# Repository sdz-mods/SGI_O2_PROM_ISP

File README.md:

# SGI O2 PROM ISP

In-system programmer for the SGI O2 system PROM. It which allows writing/dumping the system PROM via USB. This can be done at any point, with the system on or off.
Mechanically compatible with all O2 CPU modules.

## Installation instructions:

-remove Dallas socket

-remove flash IC

-solder the two FFCs

-solder Dallas socket back

-install Dallas IC

-solder the flash IC to the ISP

-mount ISP on top of Dallas IC, connect the two FFCs.

### Flashing/dumping PROM

```csh
python3 O2_FLASH_PROM.py --port COM38 --flash IP32_418_dump.bin --verify

Opening port: COM38

File : IP32_418_dump.bin  (524,288 bytes)

Flash: 524,288 bytes  |  Chunks: 128 × 4096 bytes

Flashing...

Flashing: [########################################] 100%

Flash complete.

Verifying...

Verifying: [########################################] 100%

Verify passed — flash contents match file.

python3 O2_FLASH_PROM.py --port /dev/ttyUSB0 --dump testdump.bin

Opening port: /dev/ttyUSB0

Dumping 524,288 bytes to: testdump.bin

Dumping: [########################################] 100%

Dump complete. Saved 524,288 bytes to 'testdump.bin'
```

## Contents

1.SCH_BRD - contains editable schematic and board files. Format is Eagle CAD, but they can be imported in other tools, like Kicad.

2.SCH_PDF- schematics in pdf format.

3.P&P - pick and place files

4.BOM

5.GERBER - gerber files

6.FIRMWARE - pre-built firmware to be flashed on the RP2040

7.FIRMWARE_SRC - firmware source code plus support files.

8.HOST_TOOL - host flashing script

9.PHOTOS - installation photos

## Notes

-There is a very high probabilty if you install this and flash a firmware, you won't be able to setenv -p or resetenv from PROM. This isn't related to the ISP, it happens even when swapping the flash ICs between two working motherboards.

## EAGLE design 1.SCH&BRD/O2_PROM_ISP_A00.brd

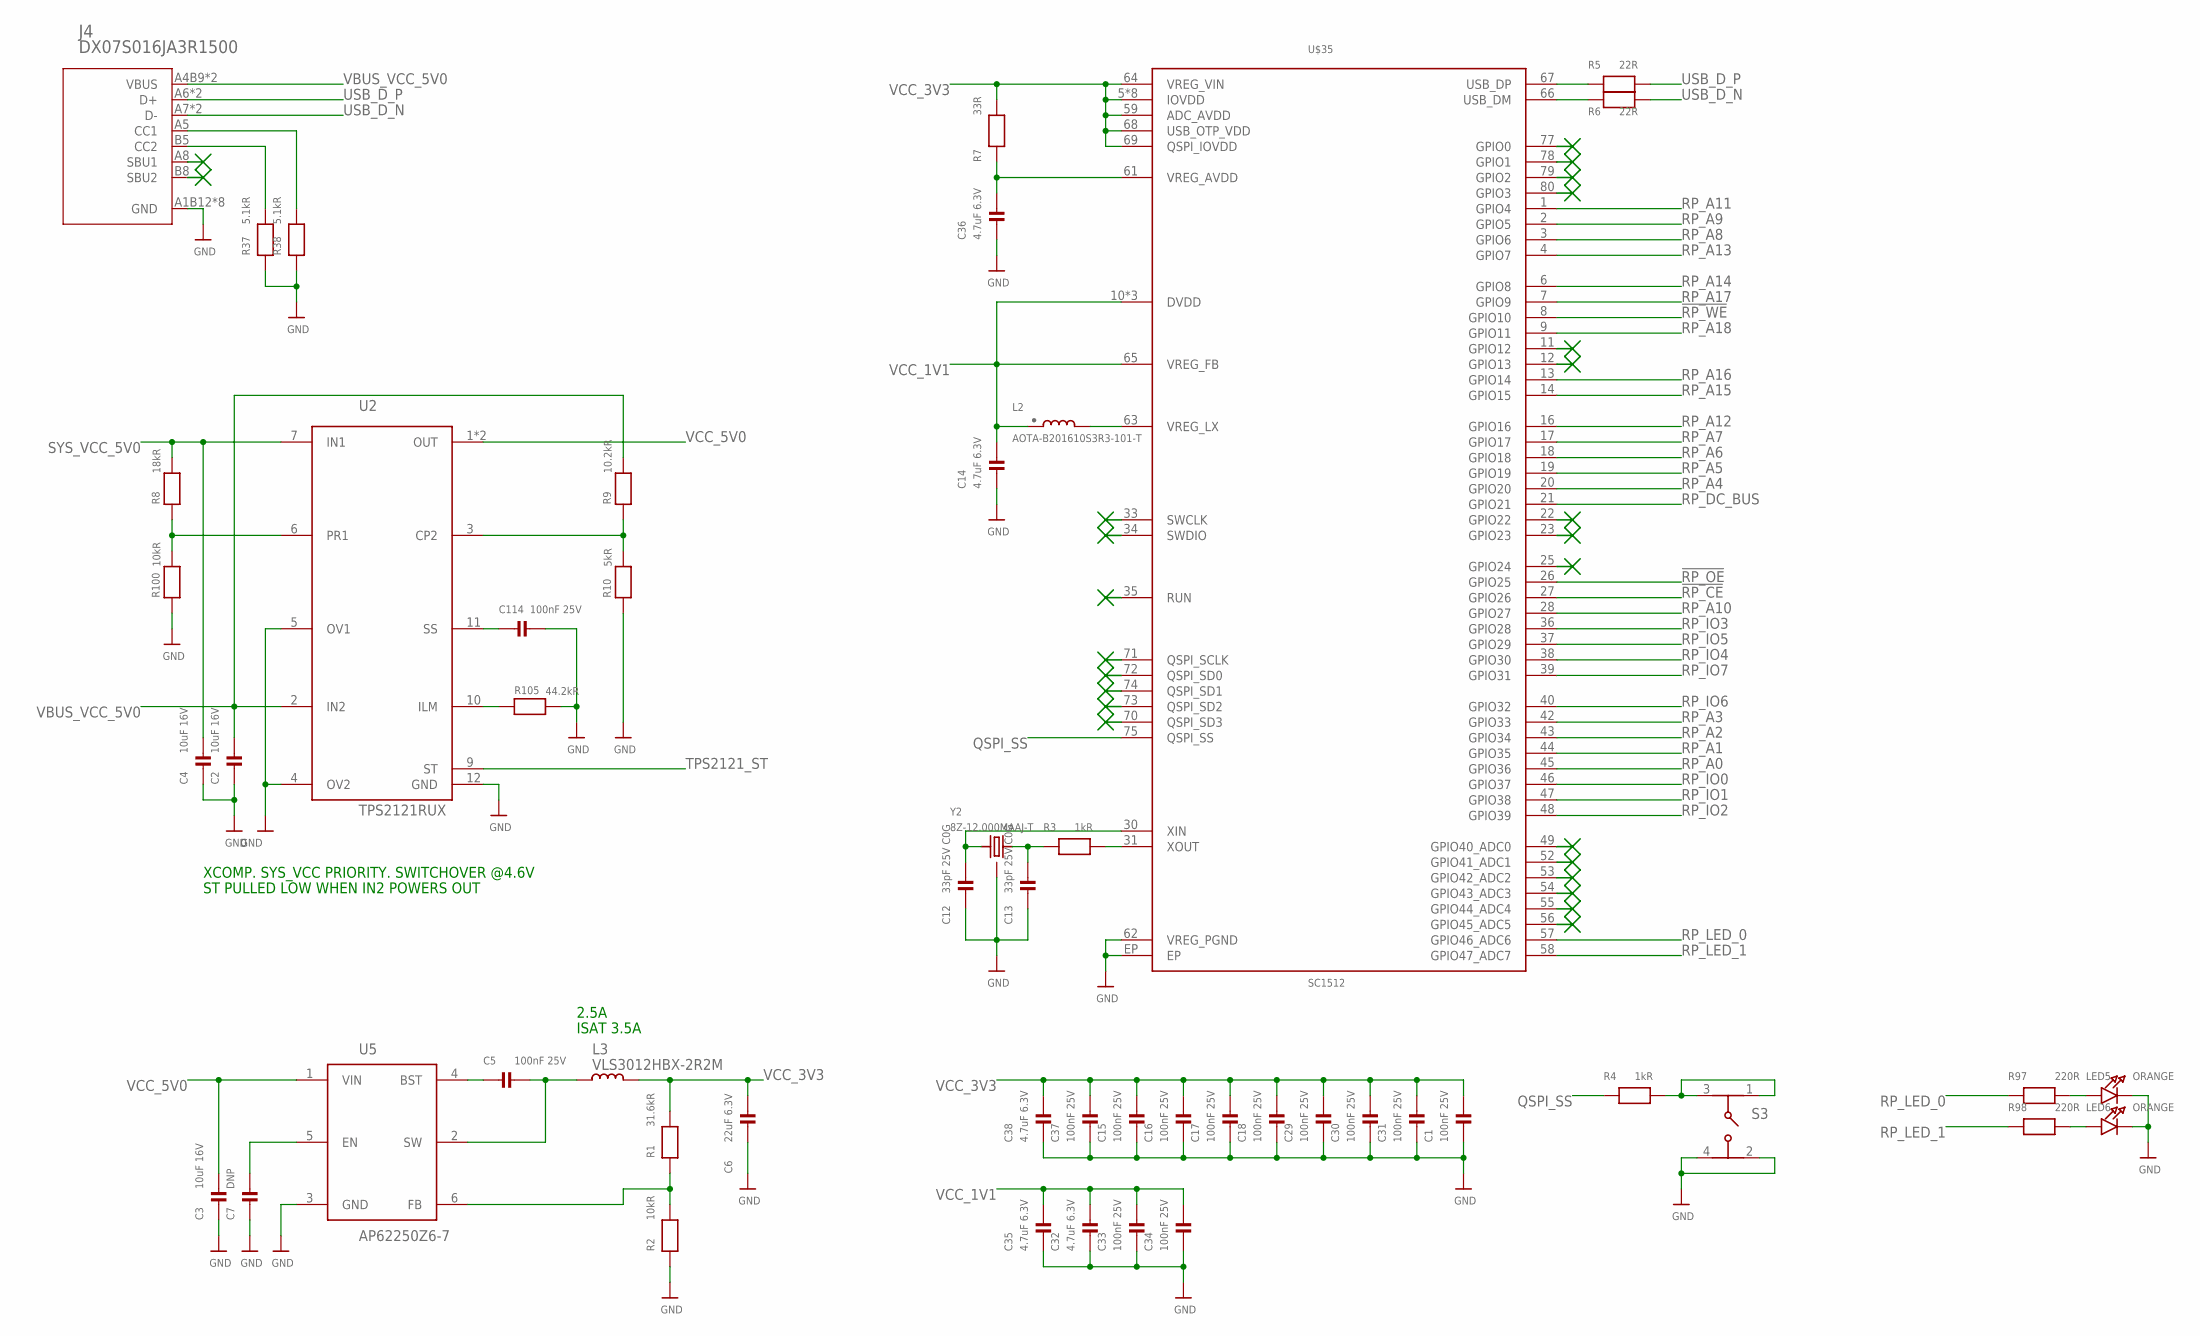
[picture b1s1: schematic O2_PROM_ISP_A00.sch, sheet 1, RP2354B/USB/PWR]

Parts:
C1, C5, C15, C16, C17, C18, C29, C30, C31, C33, C34, C37, C114: 100nF 25V; 0402D
C2, C3, C4: 10uF 16V; 0603D
C6: 22uF 6.3V; 0603D
C7: DNP; 0402D
C12, C13: 33pF 25V C0G; 0402D
C14, C32, C35, C36, C38: 4.7uF 6.3V; 0402D
J4: DX07S016JA3R1500
L2: AOTA-B201610S3R3-101-T; 0806
L3: VLS3012HBX-2R2M; VLS3012
LED5, LED6: ORANGE; CHIPLED_0402C
R1: 31.6kR; 0402D
R2, R100: 10kR; 0402D
R3, R4: 1kR; 0402D
R5, R6: 22R; 0402D
R7: 33R; 0402D
R8: 18kR; 0402D
R9: 10.2kR; 0402D
R10: 5kR; 0402D
R37, R38: 5.1kR; 0402D
R97, R98: 220R; 0402D
R105: 44.2kR; 0402D
S3: 434353045816
U2: TPS2121RUX; VQFN-HR-12
U5: AP62250Z6-7; SOTFL50P160X60-6N
U$35: SC1512
Y2: 8Z-12.000MAAJ-T; TXC-8Z-25X20

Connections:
!RP_CE: U$35.27 (GPIO26); also elsewhere on the board
!RP_OE: U$35.26 (GPIO25); also elsewhere on the board
!RP_WE: U$35.8 (GPIO10); also elsewhere on the board
GND: C1.3, C2.2, C3.2, C4.2, C6.2, C7.4, C12.3, C13.3, C14.3, C15.3, C16.3, C17.3, C18.3, C29.3, C30.3, C31.3, C32.3, C33.3, C34.3, C35.3, C36.3, C37.3, C38.3, C114.3, J4.A1B12 (GND), J4.A12/B1 (GND), J4.MH1 (GND), J4.MH2 (GND), J4.MH3 (GND), J4.MH4 (GND), J4.MP1 (GND), J4.MP2 (GND), LED5.4 (C), LED6.4 (C), R2.4 (2), R10.3 (1), R37.3 (1), R38.3 (1), R100.3 (1), R105.4 (2), S3.2 (4), S3.4 (2), U2.4 (OV2), U2.5 (OV1), U2.12 (GND), U5.3 (GND), U$35.62 (VREG_PGND), U$35.EP, Y2.2 (GND), Y2.4 (GND); also elsewhere on the board
unnamed: J4.A5 (CC1), R38.4 (2)
unnamed: R9.3 (1), R10.4 (2), U2.3 (CP2)
unnamed: J4.B5 (CC2), R37.4 (2)
unnamed: LED5.3 (A), R97.3 (1)
unnamed: LED6.3 (A), R98.3 (1)
unnamed: C13.4, R3.3 (1), Y2.3 (2)
unnamed: C12.4, U$35.30 (XIN), Y2.1
unnamed: R3.4 (2), U$35.31 (XOUT)
unnamed: R4.4 (2), S3.1 (3), S3.3 (1)
unnamed: L2.2, U$35.63 (VREG_LX)
unnamed: C5.4, U5.4 (BST)
unnamed: C5.3, L3.1 (3), U5.2 (SW)
unnamed: R1.4 (2), R2.3 (1), U5.6 (FB)
unnamed: C7.3, U5.5 (EN)
unnamed: C36.4, R7.4 (2), U$35.61 (VREG_AVDD)
unnamed: C114.4, U2.11 (SS)
unnamed: R105.3 (1), U2.10 (ILM)
unnamed: R8.3 (1), R100.4 (2), U2.6 (PR1)
QSPI_SS: R4.3 (1), U$35.75 (QSPI_SS)
RP_A0: U$35.45 (GPIO36); also elsewhere on the board
RP_A1: U$35.44 (GPIO35); also elsewhere on the board
RP_A2: U$35.43 (GPIO34); also elsewhere on the board
RP_A3: U$35.42 (GPIO33); also elsewhere on the board
RP_A4: U$35.20 (GPIO20); also elsewhere on the board
RP_A5: U$35.19 (GPIO19); also elsewhere on the board
RP_A6: U$35.18 (GPIO18); also elsewhere on the board
RP_A7: U$35.17 (GPIO17); also elsewhere on the board
RP_A8: U$35.3 (GPIO6); also elsewhere on the board
RP_A9: U$35.2 (GPIO5); also elsewhere on the board
RP_A10: U$35.28 (GPIO27); also elsewhere on the board
RP_A11: U$35.1 (GPIO4); also elsewhere on the board
RP_A12: U$35.16 (GPIO16); also elsewhere on the board
RP_A13: U$35.4 (GPIO7); also elsewhere on the board
RP_A14: U$35.6 (GPIO8); also elsewhere on the board
RP_A15: U$35.14 (GPIO15); also elsewhere on the board
RP_A16: U$35.13 (GPIO14); also elsewhere on the board
RP_A17: U$35.7 (GPIO9); also elsewhere on the board
RP_A18: U$35.9 (GPIO11); also elsewhere on the board
RP_DC_BUS: U$35.21 (GPIO21); also elsewhere on the board
RP_IO0: U$35.46 (GPIO37); also elsewhere on the board
RP_IO1: U$35.47 (GPIO38); also elsewhere on the board
RP_IO2: U$35.48 (GPIO39); also elsewhere on the board
RP_IO3: U$35.36 (GPIO28); also elsewhere on the board
RP_IO4: U$35.38 (GPIO30); also elsewhere on the board
RP_IO5: U$35.37 (GPIO29); also elsewhere on the board
RP_IO6: U$35.40 (GPIO32); also elsewhere on the board
RP_IO7: U$35.39 (GPIO31); also elsewhere on the board
RP_LED_0: R97.4 (2), U$35.57 (GPIO46_ADC6)
RP_LED_1: R98.4 (2), U$35.58 (GPIO47_ADC7)
SYS_VCC_5V0: C4.1, R8.4 (2), U2.7 (IN1); also elsewhere on the board
TPS2121_ST: U2.9 (ST); also elsewhere on the board
USB_D_C_N: R6.3 (1), U$35.66 (USB_DM)
USB_D_C_P: R5.3 (1), U$35.67 (USB_DP)
USB_D_N: J4.A7 (D-), J4.B7 (D-), R6.4 (2)
USB_D_P: J4.A6 (D+), J4.B6 (D+), R5.4 (2)
VBUS_VCC_5V0: C2.1, J4.A4B9 (VBUS), J4.B4A9 (VBUS), R9.4 (2), U2.2 (IN2)
VCC_1V1: C14.4, C32.4, C33.4, C34.4, C35.4, L2.1, U$35.10 (DVDD), U$35.32 (DVDD), U$35.51 (DVDD), U$35.65 (VREG_FB)
VCC_3V3: C1.4, C6.1, C15.4, C16.4, C17.4, C18.4, C29.4, C30.4, C31.4, C37.4, C38.4, L3.2 (4), R1.3 (1), R7.3 (1), U$35.5 (IOVDD), U$35.15 (IOVDD), U$35.24 (IOVDD), U$35.29 (IOVDD), U$35.41 (IOVDD), U$35.50 (IOVDD), U$35.59 (ADC_AVDD), U$35.60 (IOVDD), U$35.64 (VREG_VIN), U$35.68 (USB_OTP_VDD), U$35.69 (QSPI_IOVDD), U$35.76 (IOVDD)
VCC_5V0: C3.1, U2.1 (OUT), U2.8 (OUT), U5.1 (VIN); also elsewhere on the board

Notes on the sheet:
2.5A
ISAT 3.5A
XCOMP. SYS_VCC PRIORITY. SWITCHOVER @4.6V
ST PULLED LOW WHEN IN2 POWERS OUT

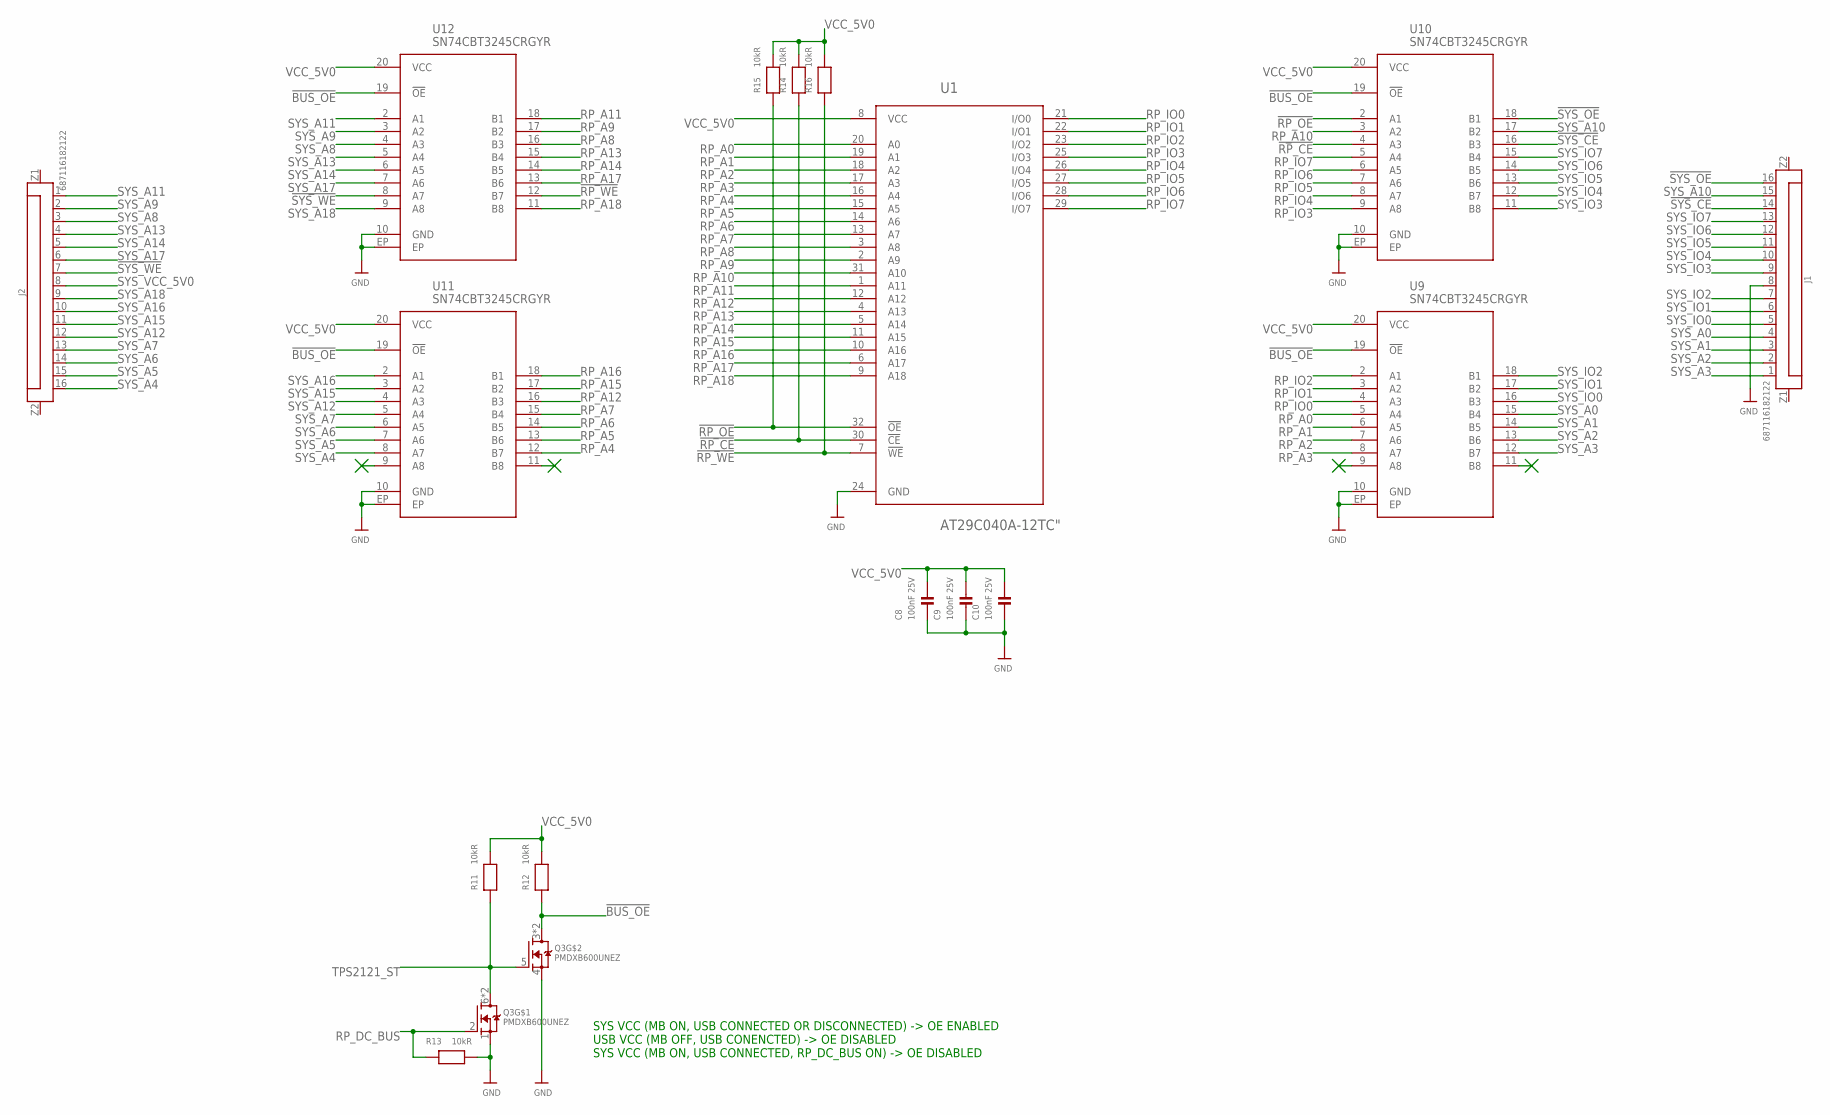
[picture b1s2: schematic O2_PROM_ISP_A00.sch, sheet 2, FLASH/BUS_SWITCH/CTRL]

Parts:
C8, C9, C10: 100nF 25V; 0402D
J1, J2: 687116182122
Q3: PMDXB600UNEZ
R11, R12, R13, R14, R15, R16: 10kR; 0402D
U1: AT29C040A-12TC"; TSOP32_8X20
U9, U10, U11, U12: SN74CBT3245CRGYR; VQFN-20

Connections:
!BUS_OE: Q3.3 (D), Q3.8 (D), R12.4 (2), U9.19 (!OE), U10.19 (!OE), U11.19 (!OE), U12.19 (!OE)
!RP_CE: R14.4 (2), U1.30 (!CE), U10.4 (A3); also elsewhere on the board
!RP_OE: R15.4 (2), U1.32 (!OE), U10.2 (A1); also elsewhere on the board
!RP_WE: R16.4 (2), U1.7 (!WE), U12.12 (B7); also elsewhere on the board
!SYS_CE: J1.14, U10.16 (B3)
!SYS_OE: J1.16, U10.18 (B1)
!SYS_WE: J2.7, U12.8 (A7)
GND: C8.3, C9.3, C10.3, J1.8, Q3.1 (S), Q3.4 (S), R13.3 (1), U1.24 (GND), U9.10 (GND), U9.EP, U10.10 (GND), U10.EP, U11.10 (GND), U11.EP, U12.10 (GND), U12.EP; also elsewhere on the board
RP_A0: U1.20 (A0), U9.5 (A4); also elsewhere on the board
RP_A1: U1.19 (A1), U9.6 (A5); also elsewhere on the board
RP_A2: U1.18 (A2), U9.7 (A6); also elsewhere on the board
RP_A3: U1.17 (A3), U9.8 (A7); also elsewhere on the board
RP_A4: U1.16 (A4), U11.12 (B7); also elsewhere on the board
RP_A5: U1.15 (A5), U11.13 (B6); also elsewhere on the board
RP_A6: U1.14 (A6), U11.14 (B5); also elsewhere on the board
RP_A7: U1.13 (A7), U11.15 (B4); also elsewhere on the board
RP_A8: U1.3 (A8), U12.16 (B3); also elsewhere on the board
RP_A9: U1.2 (A9), U12.17 (B2); also elsewhere on the board
RP_A10: U1.31 (A10), U10.3 (A2); also elsewhere on the board
RP_A11: U1.1 (A11), U12.18 (B1); also elsewhere on the board
RP_A12: U1.12 (A12), U11.16 (B3); also elsewhere on the board
RP_A13: U1.4 (A13), U12.15 (B4); also elsewhere on the board
RP_A14: U1.5 (A14), U12.14 (B5); also elsewhere on the board
RP_A15: U1.11 (A15), U11.17 (B2); also elsewhere on the board
RP_A16: U1.10 (A16), U11.18 (B1); also elsewhere on the board
RP_A17: U1.6 (A17), U12.13 (B6); also elsewhere on the board
RP_A18: U1.9 (A18), U12.11 (B8); also elsewhere on the board
RP_DC_BUS: Q3.2 (G), R13.4 (2); also elsewhere on the board
RP_IO0: U1.21 (I/O0), U9.4 (A3); also elsewhere on the board
RP_IO1: U1.22 (I/O1), U9.3 (A2); also elsewhere on the board
RP_IO2: U1.23 (I/O2), U9.2 (A1); also elsewhere on the board
RP_IO3: U1.25 (I/O3), U10.9 (A8); also elsewhere on the board
RP_IO4: U1.26 (I/O4), U10.8 (A7); also elsewhere on the board
RP_IO5: U1.27 (I/O5), U10.7 (A6); also elsewhere on the board
RP_IO6: U1.28 (I/O6), U10.6 (A5); also elsewhere on the board
RP_IO7: U1.29 (I/O7), U10.5 (A4); also elsewhere on the board
SYS_A0: J1.4, U9.15 (B4)
SYS_A1: J1.3, U9.14 (B5)
SYS_A2: J1.2, U9.13 (B6)
SYS_A3: J1.1, U9.12 (B7)
SYS_A4: J2.16, U11.8 (A7)
SYS_A5: J2.15, U11.7 (A6)
SYS_A6: J2.14, U11.6 (A5)
SYS_A7: J2.13, U11.5 (A4)
SYS_A8: J2.3, U12.4 (A3)
SYS_A9: J2.2, U12.3 (A2)
SYS_A10: J1.15, U10.17 (B2)
SYS_A11: J2.1, U12.2 (A1)
SYS_A12: J2.12, U11.4 (A3)
SYS_A13: J2.4, U12.5 (A4)
SYS_A14: J2.5, U12.6 (A5)
SYS_A15: J2.11, U11.3 (A2)
SYS_A16: J2.10, U11.2 (A1)
SYS_A17: J2.6, U12.7 (A6)
SYS_A18: J2.9, U12.9 (A8)
SYS_IO0: J1.5, U9.16 (B3)
SYS_IO1: J1.6, U9.17 (B2)
SYS_IO2: J1.7, U9.18 (B1)
SYS_IO3: J1.9, U10.11 (B8)
SYS_IO4: J1.10, U10.12 (B7)
SYS_IO5: J1.11, U10.13 (B6)
SYS_IO6: J1.12, U10.14 (B5)
SYS_IO7: J1.13, U10.15 (B4)
SYS_VCC_5V0: J2.8; also elsewhere on the board
TPS2121_ST: Q3.5 (G), Q3.6 (D), Q3.7 (D), R11.4 (2); also elsewhere on the board
VCC_5V0: C8.4, C9.4, C10.4, R11.3 (1), R12.3 (1), R14.3 (1), R15.3 (1), R16.3 (1), U1.8 (VCC), U9.20 (VCC), U10.20 (VCC), U11.20 (VCC), U12.20 (VCC); also elsewhere on the board

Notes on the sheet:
SYS VCC (MB ON, USB CONNECTED OR DISCONNECTED) -> OE ENABLED USB VCC (MB OFF, USB CONENCTED) -> OE DISABLED SYS VCC (MB ON, USB CONNECTED, RP_DC_BUS ON) -> OE DISABLED

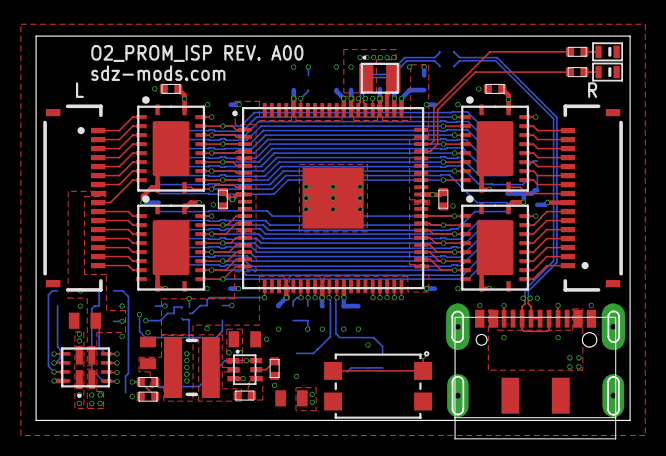
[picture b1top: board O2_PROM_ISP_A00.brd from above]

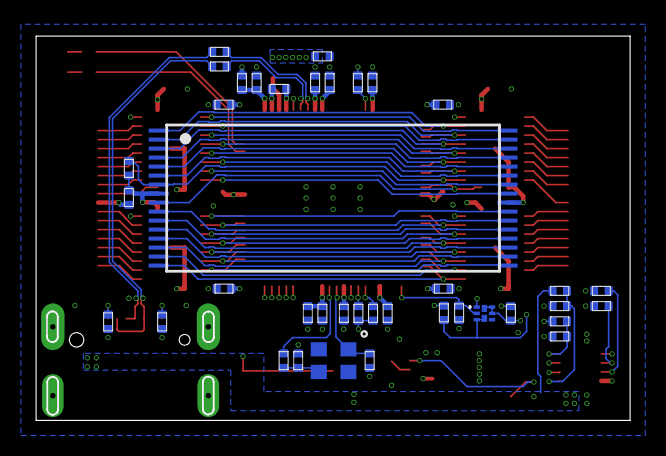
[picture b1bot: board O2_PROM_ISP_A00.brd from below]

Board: 4 copper layers, 32.9 x 21.3 mm, 68 parts (39 on the bottom side), 94 nets.

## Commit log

2026-04-06 Add environment variables management commands

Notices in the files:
parts and their libraries:
Eagle_WR-FPC: Copyright: Würth Elektronik
microbuilder: This work is placed in the public domain, and may be freely used for commercial and non-commercial work with the following conditions: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
